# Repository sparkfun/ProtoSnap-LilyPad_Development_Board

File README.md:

ProtoSnap- LilyPad Development Board
====================================

[*ProtoSnap-LilyPad Development Board (DEV-11262)*](https://www.sparkfun.com/products/11262)

The ProtoSnap LilyPad Development Board allows you to start prototyping in the world of e-textiles without a breadboard.

Repository Contents
-------------------
* **/Firmware** - LilyPad Development Board's default Arduino example code.
* **/Hardware** - All Eagle design files (.brd, .sch, .STL)

Documentation
-------------------
* [Hookup Guide](https://www.sparkfun.com/tutorials/308) - Basic hookup guide for the LilyPad Development Board.
* [Activity Guide](https://learn.sparkfun.com/tutorials/lilypad-development-board-activity-guide) - This guide will get you started with some introductory programming activities exploring each of the LilyPad pieces on the LilyPad Development Board. If you’ve never used Arduino to program before, this guide will walk you through the basics with example code to upload and explore.

Product Versions
----------------
* [DEV-11262](https://www.sparkfun.com/products/11262)- This is the standard ProtoSnap LilyPad Development Board
* [RTL-11261](https://www.sparkfun.com/products/11261)- Retail version of the ProtoSnap LilyPad Development Board. (Retired)
* [LAB-11762](https://www.sparkfun.com/products/11762)- Packaged version for educators teaching the ProtoShap LilyPad Development Board in a classroom setting. 

License Information
-------------------
The hardware is released under [Creative Commons Share-alike 3.0](http://creativecommons.org/licenses/by-sa/3.0/).

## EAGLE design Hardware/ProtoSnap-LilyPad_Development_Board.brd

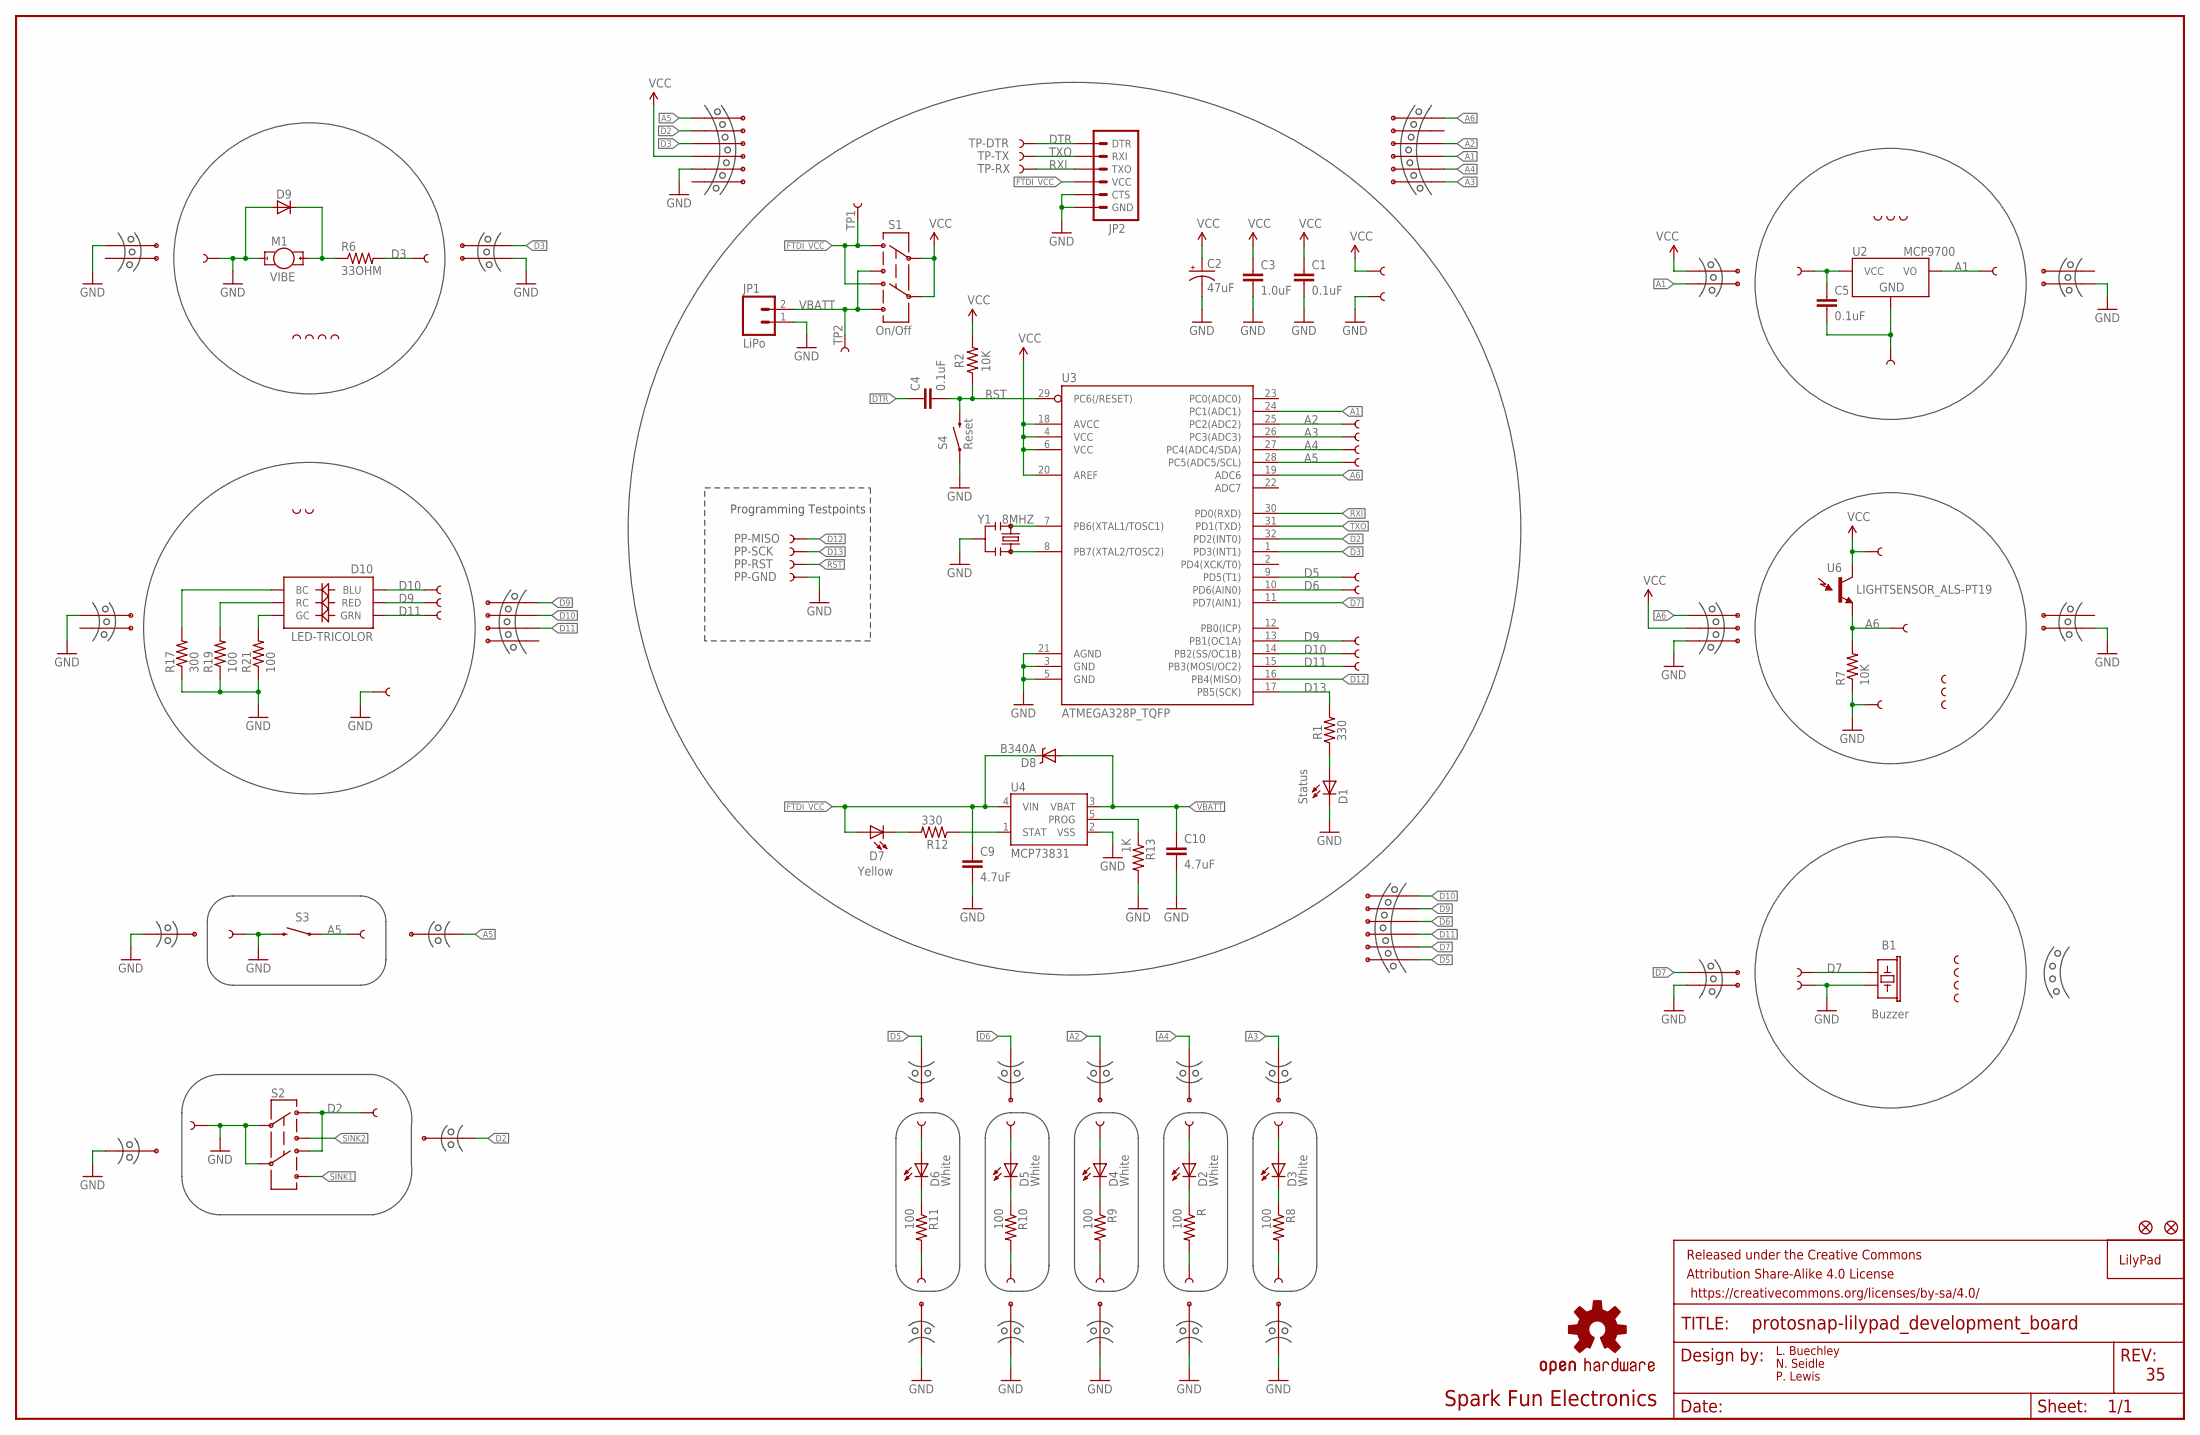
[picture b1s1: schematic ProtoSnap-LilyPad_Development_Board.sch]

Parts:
1, 2, 3, 4: SEWTAP-NOHOLE2; PETAL-NOHOLE-2SIDE
A2/16, A3/17, A4/18, A5/19: SEWTAP9; PETAL-LONG-1-2SIDE
B1: Buzzer; BUZZER-CCV
BUTTON-: SEWTAP8; PETAL-MEDIUM-2SIDE
BUTTONS: SEWTAP8; PETAL-MEDIUM-2SIDE
C1, C4, C5: 0.1uF; 0603-CAP
C2: 47uF; EIA3528
C3: 1.0uF; 0603-CAP
C9, C10: 4.7uF; 0603-CAP
D1: Status; 0603-LED-ALT1
D2, D3, D4, D5, D6: White; LED-1206
D7: Yellow; 0603-LED-ALT1
D8: B340A; SMA-DIODE
D9: DIODESOD; SOD-323
D10: LED-TRICOLOR; PLCC-6-LED
FRAME1: FRAME-LEDGER; CREATIVE_COMMONS
JP1: LiPo; JST-2-SMD
JP2: ARDUINO_SERIAL_PROGRAMSMD; 1X06-SMD
JP3, JP4: FIDUCIAL1X2; FIDUCIAL-1X2
LED+, LED+1, LED+2, LED+3, LED+4: SEWTAP6; PETAL-SMALL-2SIDE
LED-, LED-1, LED-2, LED-3, LED-4: SEWTAP6; PETAL-SMALL-2SIDE
LIGHT1, LIGHT2, LIGHT3: SEWTAP-NOHOLE2; PETAL-NOHOLE-2SIDE
LIGHT+: SEWTAP6; PETAL-SMALL-2SIDE
LIGHT-: SEWTAP6; PETAL-SMALL-2SIDE
LIGHTS: SEWTAP6; PETAL-SMALL-2SIDE
LOGO: LOGO-LPLPA; LOGO-LPA
M1: VIBE; VIBE-MOTOR-10MM-SMD
PP-GND: TEST-POINT3X5; PAD.03X.05
PP-MISO: TEST-POINT3X5; PAD.03X.05
PP-RST: TEST-POINT3X5; PAD.03X.05
PP-SCK: TEST-POINT3X5; PAD.03X.05
R, R8, R9, R10, R11, R19, R21: 100; 0603-RES
R1, R12: 330; 0603-RES
R2, R7: 10K; 0603-RES
R6: 33OHM; 0603
R13: 1K; 0603-RES
R17: 300; 0603-RES
S1: On/Off; AYZ0202
S2: AYZ0202
S3: SWITCH-MOMENTARY-2SMD-REDUNDANT; TACTILE-SWITCH-SMD
S4: Reset; TACTILE-SWITCH-SMD
SLIDEOFF: SEWTAP8; PETAL-MEDIUM-2SIDE
SLIDEON: SEWTAP8; PETAL-MEDIUM-2SIDE
TEMP1, TEMP2, TEMP3: SEWTAP-NOHOLE2; PETAL-NOHOLE-2SIDE
TEMP+: SEWTAP6; PETAL-SMALL-2SIDE
TEMP-: SEWTAP6; PETAL-SMALL-2SIDE
TEMPS: SEWTAP6; PETAL-SMALL-2SIDE
TP1, TP2: TEST-POINT3X5; PAD.03X.05
TP-DTR: TEST-POINT3X5; PAD.03X.05
TP-RX: TEST-POINT3X5; PAD.03X.05
TP-TX: TEST-POINT3X5; PAD.03X.05
U2: MCP9700; SOT23-3
U3: ATMEGA328P_TQFP; TQFP32-08
U4: MCP73831; SOT23-5
U6: LIGHTSENSOR_ALS-PT19; ALS-PT19
U$1, U$4, U$37, U$39, U$41, U$43, U$45: SEWTAP9; PETAL-LONG-1-2SIDE
U$2, U$3, U$5, U$6, U$32, U$47, U$48: MOUSE-BITE-2
U$7, U$8, U$51: MOUSE-BITE-66; MOUSE-BITE-6
U$10, U$11, U$12, U$13, U$14, U$15, U$16, U$17, U$18, U$19, U$40, U$42, U$44, U$46: MOUSE-BITE-12_HOLES; MOUST-BITE-1-(2_HOLES)
U$20: MOUSE-BITE-4
U$22, U$23, U$24, U$25, U$32-, U$33+: SEWTAP6; PETAL-SMALL-2SIDE
U$26, U$27: SEWTAP-NOHOLE2; PETAL-NOHOLE-2SIDE
U$33: MOUSE-BITE-3
U$49: MOUSE-BITE-3(NO_PADS)
U$52: OSHW-LOGOS; OSHW-LOGO-S
VIBE1, VIBE2, VIBE3, VIBE4: SEWTAP-NOHOLE2; PETAL-NOHOLE-2SIDE
VIBE+: SEWTAP6; PETAL-SMALL-2SIDE
VIBE-: SEWTAP6; PETAL-SMALL-2SIDE
Y1: 8MHZ; RESONATOR-SMD

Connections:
A1: TEMPS.1, U2.2 (VO), U3.24 (PC1(ADC1)), U$2.P$1, U$7.P$4
A2: A2/16.1, U3.25 (PC2(ADC2)), U$7.P$3, U$12.P$1
A3: A3/17.1, U3.26 (PC3(ADC3)), U$7.P$6, U$13.P$1
A4: A4/18.1, U3.27 (PC4(ADC4/SDA)), U$7.P$5, U$14.P$1
A5: A5/19.1, BUTTONS.1, S3.1, S3.2 (1), U3.28 (PC5(ADC5/SCL)), U$8.P$1, U$40.P$1
A6: LIGHTS.1, R7.2, U3.19 (ADC6), U6.E (E1), U$7.P$1, U$33.P$1
BLUE: D10.CB (BC), R17.2
D2: S2.3 (1), S2.6 (4), SLIDEON.1, U3.32 (PD2(INT0)), U$8.P$2, U$46.P$1
D3: R6.2, U3.1 (PD3(INT1)), U$5.P$1, U$8.P$3, VIBE+.1
D5: U3.9 (PD5(T1)), U$10.P$1, U$41.1, U$51.P$1
D6: U3.10 (PD6(AIN0)), U$1.1, U$11.P$1, U$51.P$4
D7: B1.+ (1), U3.11 (PD7(AIN1)), U$32.P$2, U$33+.1, U$51.P$2
D9: D10.AR (RED), U3.13 (PB1(OC1A)), U$20.P$4, U$22.1, U$37.1, U$51.P$5
D10: D10.AB (BLU), U3.14 (PB2(SS/OC1B)), U$20.P$3, U$24.1, U$39.1, U$51.P$6
D11: D10.AG (GRN), U3.15 (PB3(MOSI/OC2)), U$4.1, U$20.P$2, U$23.1, U$51.P$3
D12: PP-MISO.P$1, U3.16 (PB4(MISO))
D13: PP-SCK.P$1, R1.2, U3.17 (PB5(SCK))
DTR: C4.1, JP2.1 (DTR), TP-DTR.P$1
FTDI_VCC: C9.1, D7.A, D8.C, JP2.4 (VCC), S1.3 (1), S1.6 (4), TP1.P$1, U4.4 (VIN)
GND: B1.- (2), BUTTON-.1, C1.2, C2.C (-), C3.2, C5.2, C9.2, C10.2, D1.C, D9.2 (A), JP1.1, JP2.5 (CTS), JP2.6 (GND), LIGHT-.1, M1.P$2 (-), PP-GND.P$1, R7.1, R13.2, R17.1, R19.1, R21.1, S2.2, S2.5, S3.3 (2), S3.4 (2), S4.1, S4.2 (1), SLIDEOFF.1, TEMP-.1, U2.3 (GND), U3.3 (GND), U3.5 (GND), U3.21 (AGND), U4.2 (VSS), U$3.P$1, U$5.P$2, U$6.P$1, U$8.P$5, U$15.P$1, U$16.P$1, U$17.P$1, U$18.P$1, U$19.P$1, U$25.1, U$32.P$1, U$32-.1, U$33.P$3, U$42.P$1, U$43.1, U$44.P$1, U$47.P$1, U$48.P$1, VIBE-.1, Y1.2
GRN1: D10.CG (GC), R21.2
unnamed: U3.7 (PB6(XTAL1/TOSC1)), Y1.1
unnamed: D1.A, R1.1
unnamed: U3.8 (PB7(XTAL2/TOSC2)), Y1.3
unnamed: D9.1 (C), M1.P$1 (+), R6.1
unnamed: D2.C, R.1
unnamed: D2.A, LED+.1
unnamed: LED-.1, R.2
unnamed: D3.C, R8.1
unnamed: D3.A, LED+1.1
unnamed: LED-1.1, R8.2
unnamed: D4.C, R9.1
unnamed: D4.A, LED+2.1
unnamed: LED-2.1, R9.2
unnamed: D5.C, R10.1
unnamed: D5.A, LED+3.1
unnamed: LED-3.1, R10.2
unnamed: D6.C, R11.1
unnamed: D6.A, LED+4.1
unnamed: LED-4.1, R11.2
unnamed: D7.C, R12.2
PROG: R13.1, U4.5 (PROG)
RED1: D10.CR (RC), R19.2
RST: C4.2, PP-RST.P$1, R2.1, S4.3 (2), S4.4 (2), U3.29 (PC6(/RESET))
RXI: JP2.3 (TXO), TP-RX.P$1, U3.30 (PD0(RXD))
SINK1: S2.4 (6)
SINK2: S2.1 (3)
STAT: R12.1, U4.1 (STAT)
TXO: JP2.2 (RXI), TP-TX.P$1, U3.31 (PD1(TXD))
VBATT: C10.1, D8.A, JP1.2, S1.1 (3), S1.4 (6), TP2.P$1, U4.3 (VBAT)
VCC: C1.1, C2.A (+), C3.1, C5.1, LIGHT+.1, R2.2, S1.2, S1.5, TEMP+.1, U2.1 (VCC), U3.4 (VCC), U3.6 (VCC), U3.18 (AVCC), U3.20 (AREF), U6.C (C1), U$2.P$2, U$8.P$4, U$33.P$2, U$45.1

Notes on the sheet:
Spark Fun Electronics
L. Buechley
N. Seidle
P. Lewis
Programming Testpoints

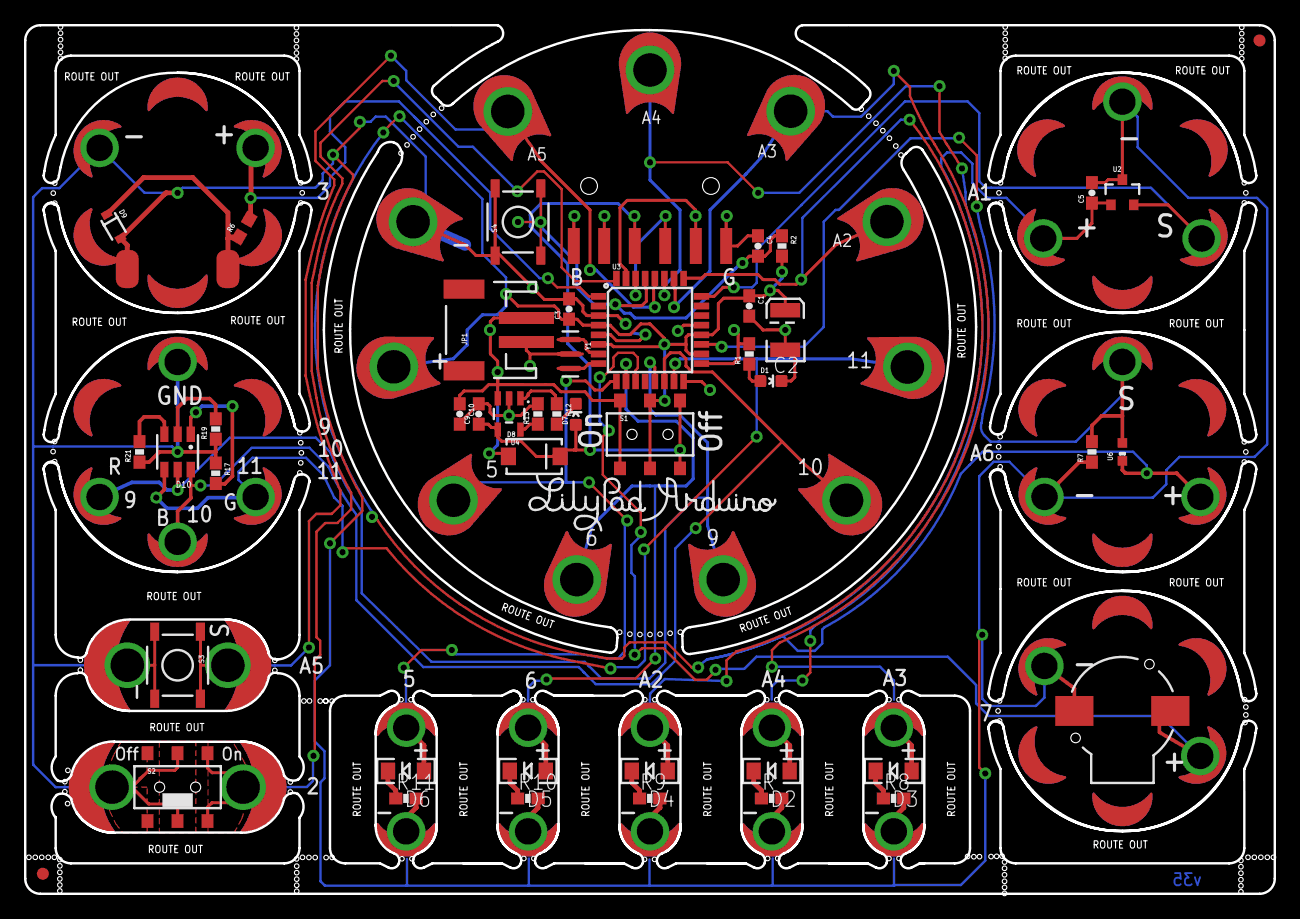
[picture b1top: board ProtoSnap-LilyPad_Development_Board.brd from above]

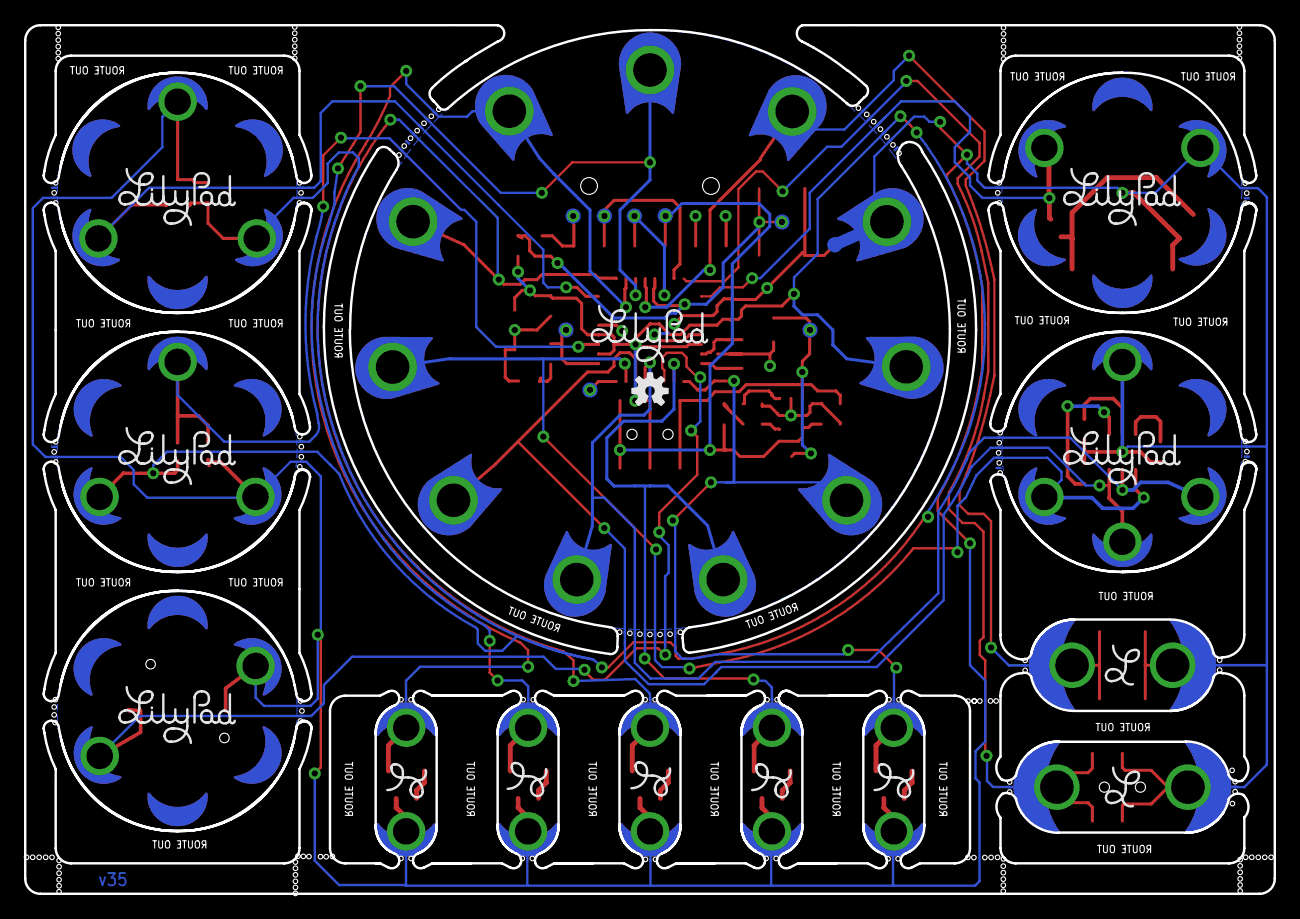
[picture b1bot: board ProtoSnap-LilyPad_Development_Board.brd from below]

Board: 2 copper layers, 104.1 x 72.4 mm, 158 parts (23 on the bottom side), 49 nets.

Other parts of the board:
LOGO1, LOGO2, LOGO3, LOGO4, LOGO5, LOGO6, LOGO7: LOGO-LPL; LOGO-L
U$9: LOGO-LILYPAD
U$21, U$29, U$30, U$31, U$35: LOGO-LPLP; LOGO-LILYPAD
U$28, U$34, U$36, U$38, U$50: LILYPAD-BRD-LAYERS-SMALL

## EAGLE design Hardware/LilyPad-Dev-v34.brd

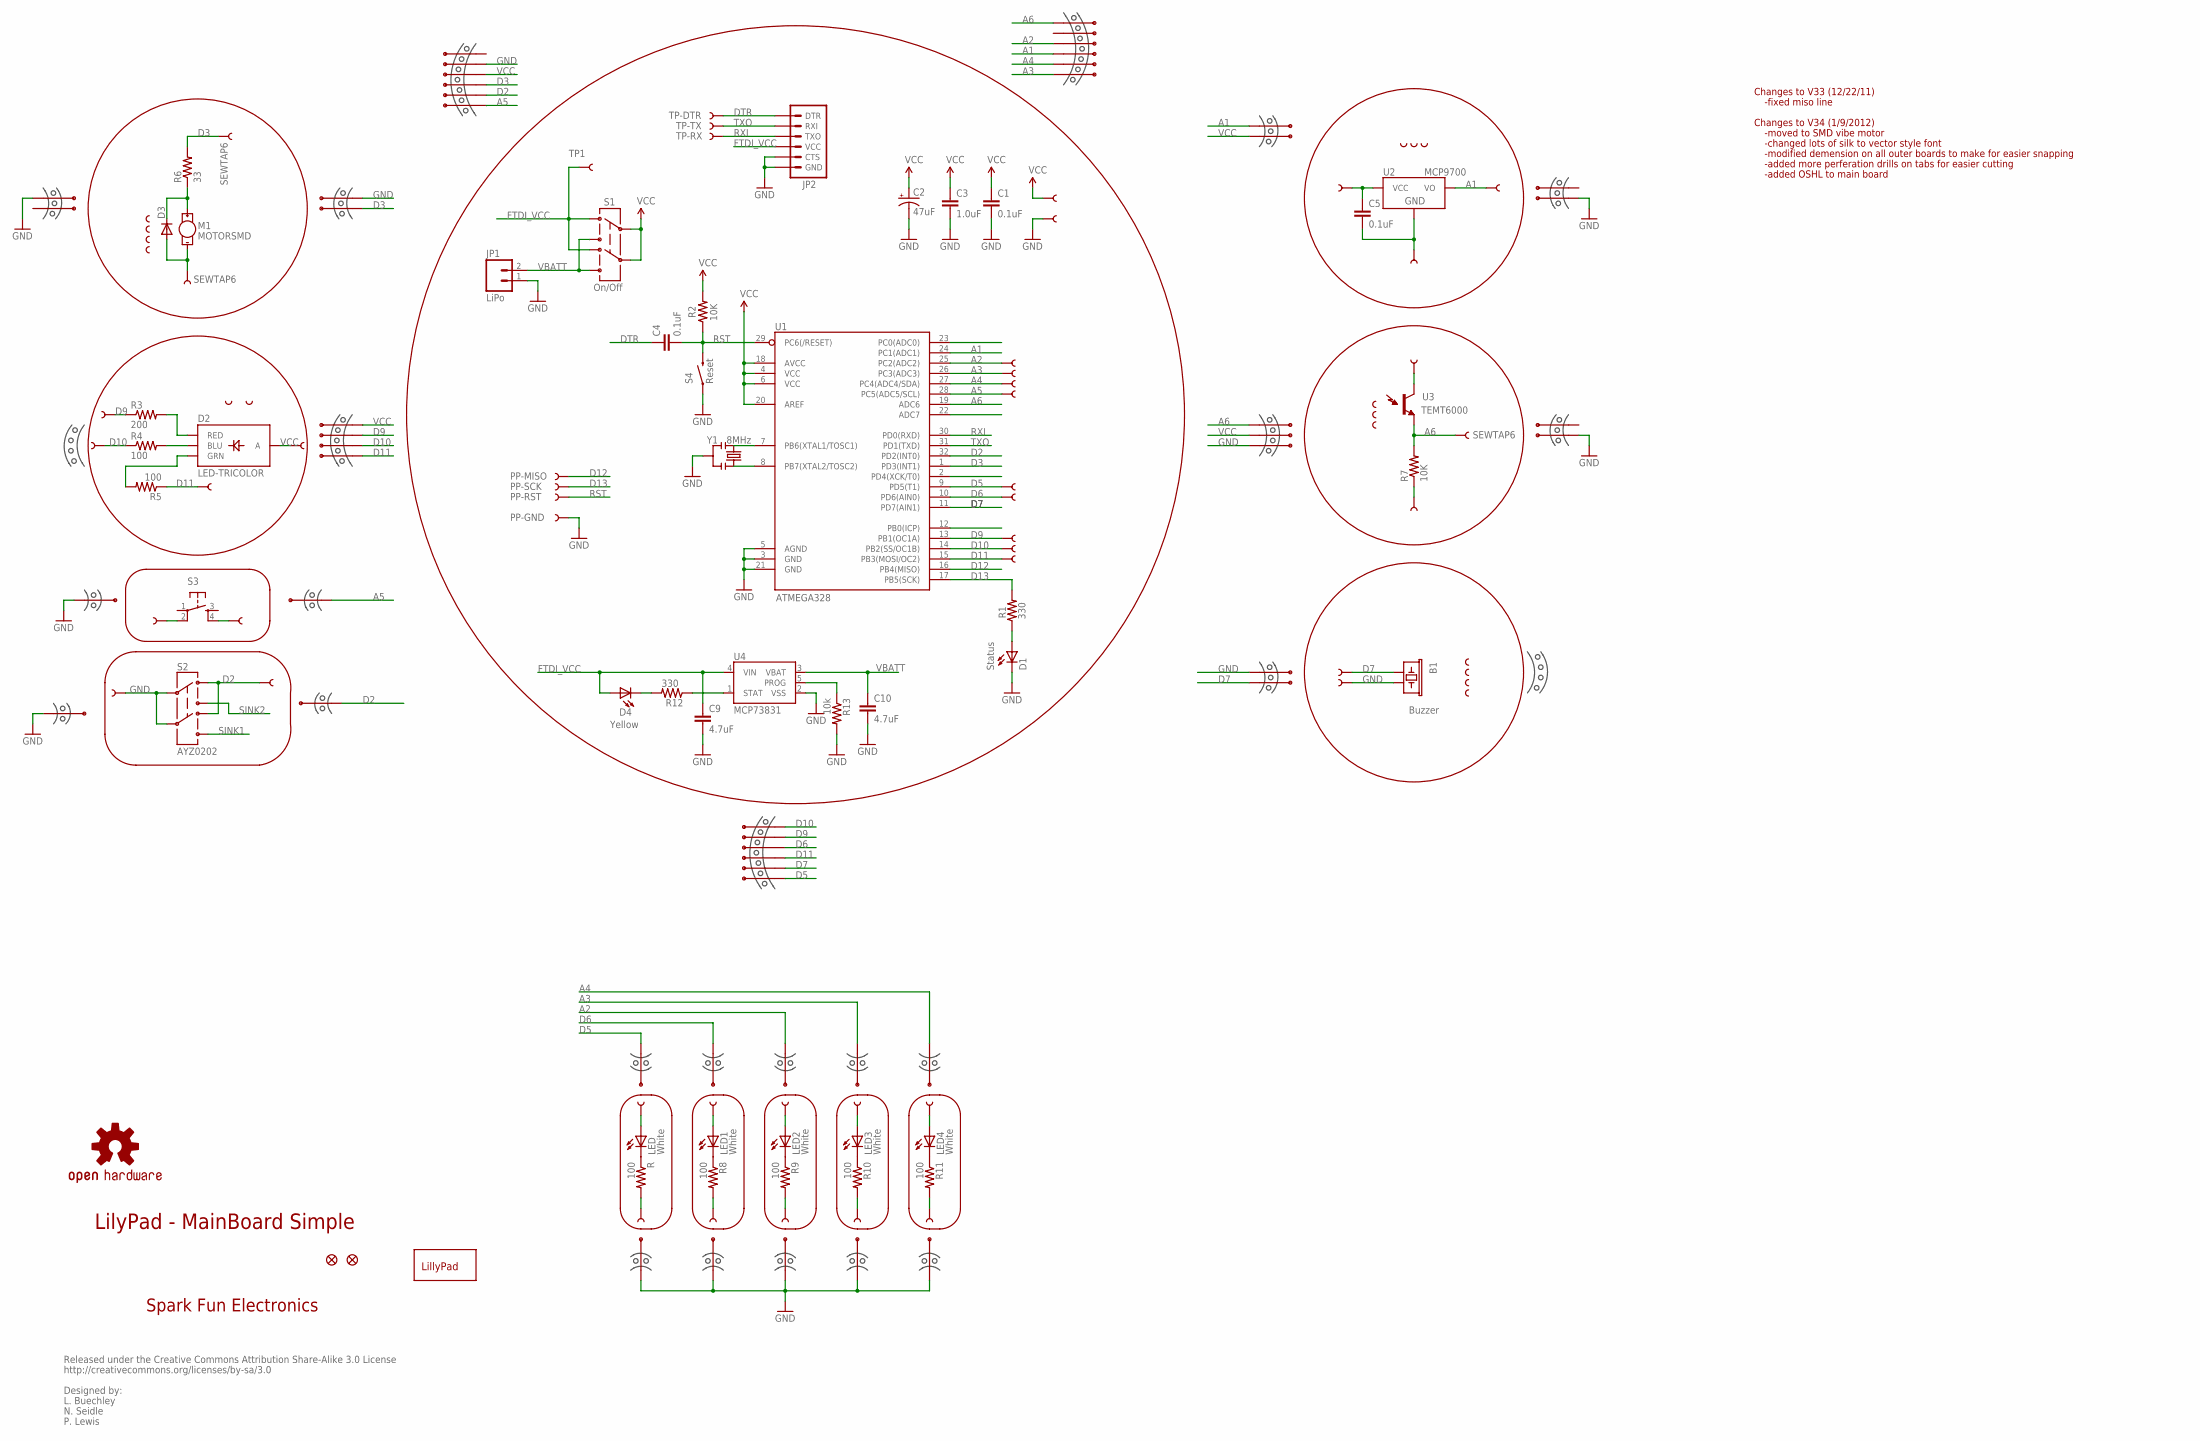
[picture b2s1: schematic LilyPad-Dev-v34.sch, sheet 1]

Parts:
1, 2, 3, 4: SEWTAP-NOHOLE2; PETAL-NOHOLE-2SIDE
A2/16, A3/17, A4/18, A5/19: SEWTAP9; PETAL-LONG-1-2SIDE
B1: Buzzer; BUZZER-CCV
BUTTON-: SEWTAP8; PETAL-SMALL
BUTTONS: SEWTAP8; PETAL-SMALL
C1, C4: 0.1uF; 0402-CAP
C2: 47uF; EIA3528
C3: 1.0uF; 0402-CAP
C5: 0.1uF; 0603-CAP
C9, C10: 4.7uF; 0402-CAP
D1: Status; LED-0603
D2: LED-TRICOLOR; LED-TRICOLOR-SMD
D3: DIODESOD; SOD-323
D4: Yellow; LED-0603
JP1: LiPo; JST-2-SMD
JP2: ARDUINO_SERIAL_PROGRAMSMD; 1X06-SMD
JP3, JP4: FIDUCIAL1X2; FIDUCIAL-1X2
LED, LED1, LED2, LED3, LED4: White; LED-1206
LED+, LED+1, LED+2, LED+3, LED+4: SEWTAP6; PETAL-SMALL-2SIDE
LED-, LED-1, LED-2, LED-3, LED-4: SEWTAP6; PETAL-SMALL-2SIDE
LIGHT1, LIGHT2, LIGHT3: SEWTAP-NOHOLE2; PETAL-NOHOLE-2SIDE
LIGHT+: SEWTAP6; PETAL-SMALL
LIGHT-: SEWTAP6; PETAL-SMALL
LIGHTS: SEWTAP6; PETAL-SMALL
LOGO: LOGO-LPLPA; LOGO-LPA
M1: MOTORSMD; VIBE-MOTOR-10MM-SMD
PP-GND: TEST-POINT3X5; PAD.03X.05
PP-MISO: TEST-POINT3X5; PAD.03X.05
PP-RST: TEST-POINT3X5; PAD.03X.05
PP-SCK: TEST-POINT3X5; PAD.03X.05
R, R8, R9, R10, R11: 100; 0603-RES
R1, R12: 330; 0402-RES
R2, R7: 10K; 0402-RES
R3: 200; 0402-RES
R4, R5: 100; 0402-RES
R6: 33; 0402-RES
R13: 10k; 0402-RES
S1: On/Off; AYZ0202
S2: AYZ0202
S3: TAC_SWITCHSMD; TACTILE_SWITCH_SMD
S4: Reset; TACTILE_SWITCH_SMD
SLIDEOFF: SEWTAP8; PETAL-SMALL
SLIDEON: SEWTAP8; PETAL-SMALL
TEMP1, TEMP2, TEMP3: SEWTAP-NOHOLE2; PETAL-NOHOLE-2SIDE
TEMP+: SEWTAP6; PETAL-SMALL
TEMP-: SEWTAP6; PETAL-SMALL
TEMPS: SEWTAP6; PETAL-SMALL
TP1: TEST-POINT3X5; PAD.03X.05
TP-DTR: TEST-POINT3X5; PAD.03X.05
TP-RX: TEST-POINT3X5; PAD.03X.05
TP-TX: TEST-POINT3X5; PAD.03X.05
U1: ATMEGA328; TQFP32-08
U2: MCP9700; SOT23-3
U3: TEMT6000; TEMT6000-SEN
U4: MCP73831; SOT23-5
U$1, U$4, U$37, U$39, U$41, U$43, U$45: SEWTAP9; PETAL-LONG-1-2SIDE
U$2, U$3, U$5, U$6, U$32, U$47: MOUSE-BITE-2
U$7, U$8, U$51: MOUSE-BITE-66; MOUSE-BITE-6
U$10, U$11, U$12, U$13, U$14, U$15, U$16, U$17, U$18, U$19, U$40, U$42, U$44, U$46: MOUSE-BITE-12_HOLES; MOUST-BITE-1-(2_HOLES)
U$20: MOUSE-BITE-4
U$22, U$23, U$24, U$25: SEWTAP6; PETAL-SMALL-2SIDE
U$26, U$27: SEWTAP-NOHOLE2; PETAL-NOHOLE-2SIDE
U$32-, U$33+: SEWTAP6; PETAL-SMALL
U$33: MOUSE-BITE-3
U$48, U$49: MOUSE-BITE-3(NO_PADS)
U$52: OSHW-LOGOS; OSHW-LOGO-S
VIBE1, VIBE2, VIBE3, VIBE4: SEWTAP-NOHOLE2; PETAL-NOHOLE-2SIDE
VIBE+: SEWTAP6; PETAL-SMALL
VIBE-: SEWTAP6; PETAL-SMALL
Y1: 8MHz; RESONATOR-SMD

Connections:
A1: TEMPS.1, U1.24 (PC1(ADC1)), U2.2 (VO), U$2.P$1, U$7.P$4
A2: A2/16.1, U1.25 (PC2(ADC2)), U$7.P$3, U$12.P$1
A3: A3/17.1, U1.26 (PC3(ADC3)), U$7.P$6, U$13.P$1
A4: A4/18.1, U1.27 (PC4(ADC4/SDA)), U$7.P$5, U$14.P$1
A5: A5/19.1, BUTTONS.1, S3.2, U1.28 (PC5(ADC5/SCL)), U$8.P$1, U$40.P$1
A6: LIGHTS.1, R7.2, U1.19 (ADC6), U3.EMITTER (E1), U$7.P$1, U$33.P$1
BLU: D2.B (BLU), R4.2
D2: S2.3 (1), S2.6 (4), SLIDEON.1, U1.32 (PD2(INT0)), U$8.P$2, U$46.P$1
D3: R6.2, U1.1 (PD3(INT1)), U$5.P$1, U$8.P$3, VIBE+.1
D5: U1.9 (PD5(T1)), U$10.P$1, U$41.1, U$51.P$1
D6: U1.10 (PD6(AIN0)), U$1.1, U$11.P$1, U$51.P$4
D7: B1.+ (1), U1.11 (PD7(AIN1)), U$32.P$2, U$33+.1, U$51.P$2
D9: R3.1, U1.13 (PB1(OC1A)), U$20.P$3, U$22.1, U$37.1, U$51.P$5
D10: R4.1, U1.14 (PB2(SS/OC1B)), U$20.P$2, U$24.1, U$39.1, U$51.P$6
D11: R5.1, U1.15 (PB3(MOSI/OC2)), U$4.1, U$20.P$1, U$23.1, U$51.P$3
D12: PP-MISO.P$1, U1.16 (PB4(MISO))
D13: PP-SCK.P$1, R1.2, U1.17 (PB5(SCK))
DTR: C4.1, JP2.1 (DTR), TP-DTR.P$1
FTDI_VCC: C9.1, D4.A, JP2.4 (VCC), S1.3 (1), S1.6 (4), TP1.P$1, U4.4 (VIN)
GND: B1.- (2), BUTTON-.1, C1.2, C2.C (-), C3.2, C5.2, C9.2, C10.2, D1.C, D3.2 (A), JP1.1, JP2.5 (CTS), JP2.6 (GND), LIGHT-.1, M1.P$2 (-), PP-GND.P$1, R7.1, R13.2, S2.2, S2.5, S3.4, S4.1, SLIDEOFF.1, TEMP-.1, U1.3 (GND), U1.5 (AGND), U1.21 (GND), U2.3 (GND), U4.2 (VSS), U$3.P$1, U$5.P$2, U$6.P$1, U$8.P$5, U$15.P$1, U$16.P$1, U$17.P$1, U$18.P$1, U$19.P$1, U$32.P$1, U$32-.1, U$33.P$3, U$42.P$1, U$43.1, U$44.P$1, U$47.P$1, VIBE-.1, Y1.2
GRN: D2.G (GRN), R5.2
unnamed: U1.7 (PB6(XTAL1/TOSC1)), Y1.1
unnamed: D1.A, R1.1
unnamed: U1.8 (PB7(XTAL2/TOSC2)), Y1.3
unnamed: D3.1 (C), M1.P$1 (+), R6.1
unnamed: LED.C, R.1
unnamed: LED.A, LED+.1
unnamed: LED-.1, R.2
unnamed: LED1.C, R8.1
unnamed: LED1.A, LED+1.1
unnamed: LED-1.1, R8.2
unnamed: LED2.C, R9.1
unnamed: LED2.A, LED+2.1
unnamed: LED-2.1, R9.2
unnamed: LED3.C, R10.1
unnamed: LED3.A, LED+3.1
unnamed: LED-3.1, R10.2
unnamed: LED4.C, R11.1
unnamed: LED4.A, LED+4.1
unnamed: LED-4.1, R11.2
unnamed: D4.C, R12.2
PROG: R13.1, U4.5 (PROG)
RED: D2.R (RED), R3.2
RST: C4.2, PP-RST.P$1, R2.1, S4.3 (2), U1.29 (PC6(/RESET))
RXI: JP2.3 (TXO), TP-RX.P$1, U1.30 (PD0(RXD))
SINK1: S2.4 (6)
SINK2: S2.1 (3)
STAT: R12.1, U4.1 (STAT)
TXO: JP2.2 (RXI), TP-TX.P$1, U1.31 (PD1(TXD))
VBATT: C10.1, JP1.2, S1.1 (3), S1.4 (6), U4.3 (VBAT)
VCC: C1.1, C2.A (+), C3.1, C5.1, D2.A, LIGHT+.1, R2.2, S1.2, S1.5, TEMP+.1, U1.4 (VCC), U1.6 (VCC), U1.18 (AVCC), U1.20 (AREF), U2.1 (VCC), U3.COLLECTOR (C1), U$2.P$2, U$8.P$4, U$20.P$4, U$25.1, U$33.P$2, U$45.1

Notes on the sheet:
LilyPad - MainBoard Simple
Spark Fun Electronics
Released under the Creative Commons Attribution Share-Alike 3.0 License
http://creativecommons.org/licenses/by-sa/3.0
Designed by:
L. Buechley
N. Seidle
P. Lewis
Changes to V33 (12/22/11)
-fixed miso line
Changes to V34 (1/9/2012)
-moved to SMD vibe motor
-changed lots of silk to vector style font
-modified demension on all outer boards to make for easier snapping
-added more perferation drills on tabs for easier cutting
-added OSHL to main board

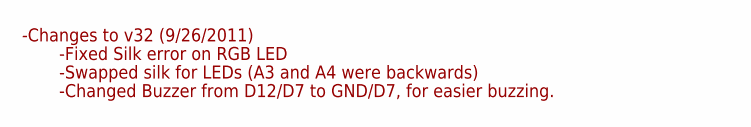
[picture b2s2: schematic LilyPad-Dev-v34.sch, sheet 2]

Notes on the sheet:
-Changes to v32 (9/26/2011)
-Fixed Silk error on RGB LED
-Swapped silk for LEDs (A3 and A4 were backwards)
-Changed Buzzer from D12/D7 to GND/D7, for easier buzzing.

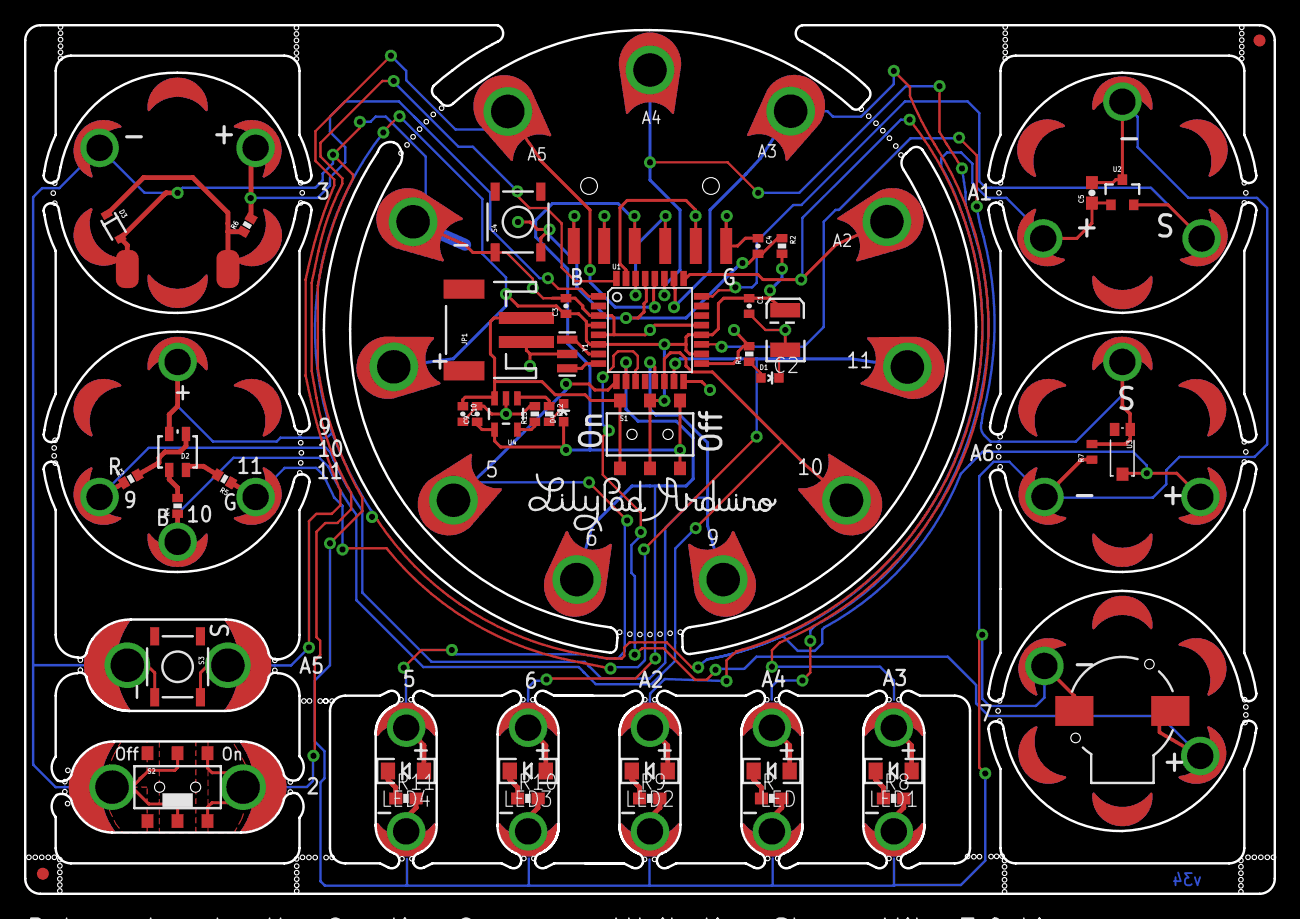
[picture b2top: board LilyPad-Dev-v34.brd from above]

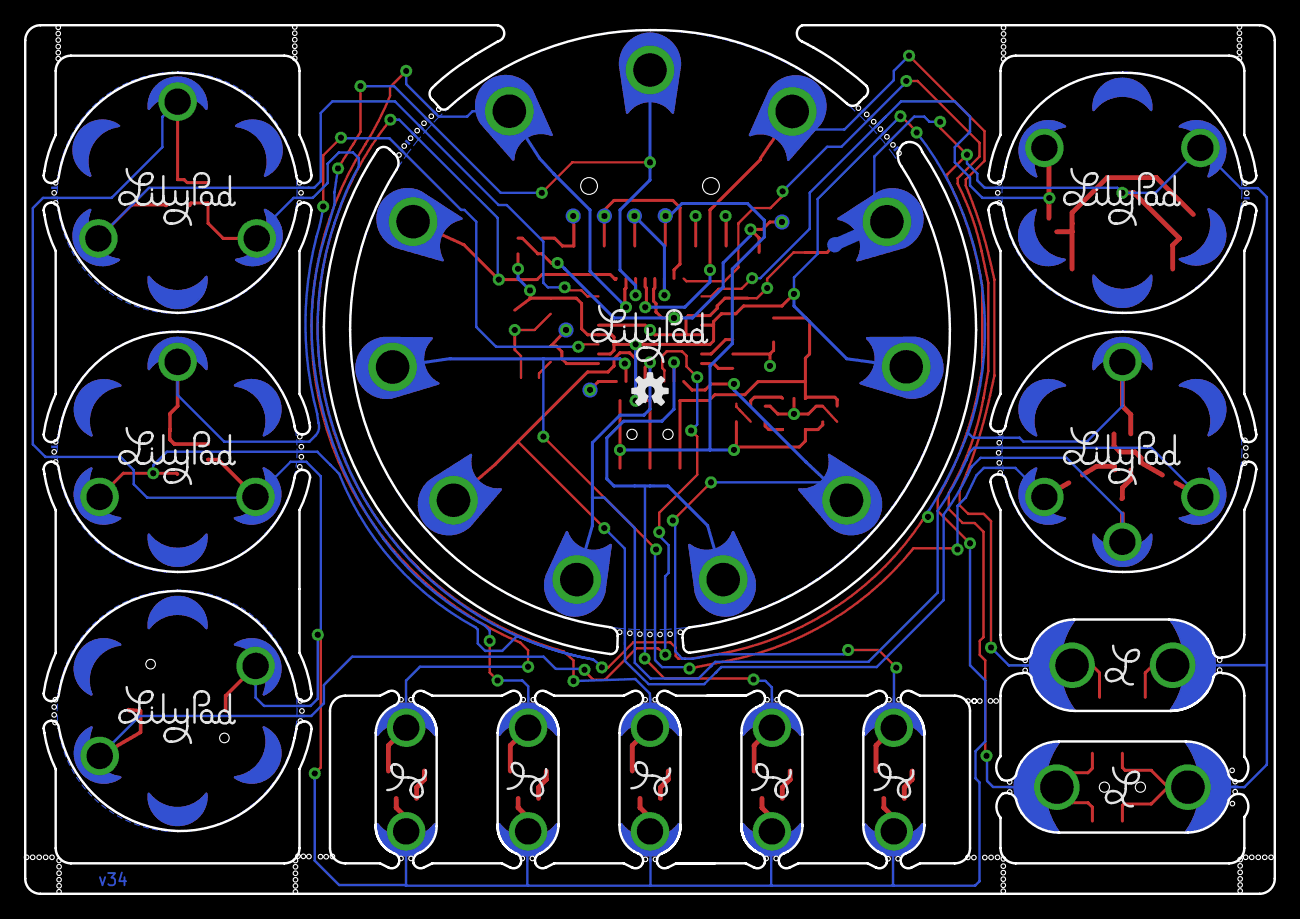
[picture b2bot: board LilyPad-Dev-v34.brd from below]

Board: 2 copper layers, 104.1 x 72.4 mm, 155 parts (22 on the bottom side), 49 nets.

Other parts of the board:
LOGO1, LOGO2, LOGO3, LOGO4, LOGO5, LOGO6, LOGO7: LOGO-LPL; LOGO-L
U$9: LOGO-LILYPAD
U$21, U$29, U$30, U$31, U$35: LOGO-LPLP; LOGO-LILYPAD
U$28, U$34, U$36, U$38, U$50: LILYPAD-BRD-LAYERS-SMALL

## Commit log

2013-03-25 Files as being sent out for prototype.
    Moved a bunch of components to 0603.
    Had to move a lot of components just slightly and re-route traces.
2013-11-19 Adding README
2013-11-19 Adding current board files
2014-01-02 finishing up v35 - a few things
    -updated LILYPAD-BRD-LAYERS.pac to include fixed polygons.
    -updated to ledger in schematic, updated "designed by" text objects.
    re-spaced schematic for more even look
    -updated to 1:1 (+fake traces) footprint on resonator package
2014-02-07 Added diode from VBATT to VBUS
    also updated to flags in schematic.
2014-02-10 Fix snap drill hits
    spaced out drill hits on the bottom right tab division line. They were
    too close and GP did not like that.
2014-05-01 Updated momentary buttons to new package
2014-05-01 Replaced resonator device to SparkFun-FreqCtrl.lbr
    This used to be from SFE-testing-library, and now it's linked to the
    "official/proven" SFE library.
2014-05-01 Schematic cleanup and a few brd part nudges
    -Fixed 4 way junction in reset net.
    -Moved a few vias, and parts to avoid DRC clearance errors.
2015-02-06 fix gaps in dimension layer
2015-03-05 Common Cathode LED, ALS-PT19 light sensor
    Also added measures and "route out" text.
2015-04-06 Schematic cleanup
    -Fixed 4-way junction off of MCP73831
    -cleaned up nets off of snap-able leds
    -added sch note and box for programming testpoints
    -moved to flag label on D7
    -removed value labels on pedals near motor
    -corrected diode prefixes
2015-04-06 more schematic cleanup
2015-04-06 removed sheet 2
    had notes about old revisions, this is now unnecessary
2015-04-06 Adding Prod IDs (not 100% done)
    Also had to reroute traces off of IC
2015-04-07 fixing some acid traps and scooting some component
2017-12-20 Create lilypad_dev_v11.ino
    -Adding Pete Lewis' default example code for the LilyPad ProtoSnap Development Board that is linked in SparkFun's old tutorials [ [https://www.sparkfun.com/tutorials/308](https://www.sparkfun.com/tut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
    -Converting .pde to .ino
2017-12-27 Update lilypad_dev_v11.ino
    Combine old method of setting a button/switch HIGH for a pull-up [ [https://www.arduino.cc/en/Tutorial/DigitalPins](https://www.arduino.cc/en/Tutorial/DigitalPins) ]:
    //Switch
    pinMode(switchPin, INPUT); // set the switch as an input
    digitalWrite(switchPin, HIGH); // enable the pull-up resistor
    //Button
    pinMode(buttonPin, INPUT); // set the pin as an input
2017-12-27 Rename Firmware/lilypad_dev_v11/lilypad_dev_v11.ino to Firmware/LilyPadDev_v11rev/LilyPadDev_v11rev.ino
    update file name to reflect changes
2018-01-08 Update README.md
    - Add link for Activity Guide.
    -Add note about the retail version retired.
    - Add lab pack version.

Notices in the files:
parts and their libraries:
SparkFun-Aesthetics: Licensing: CC v3.0 Share-Alike You are welcome to use this library for commercial purposes.
SparkFun-Aesthetics: Released under the Creative Commons Attribution Share-Alike 4.0 License
SparkFun-Aesthetics: https://creativecommons.org/licenses/by-sa/4.0
